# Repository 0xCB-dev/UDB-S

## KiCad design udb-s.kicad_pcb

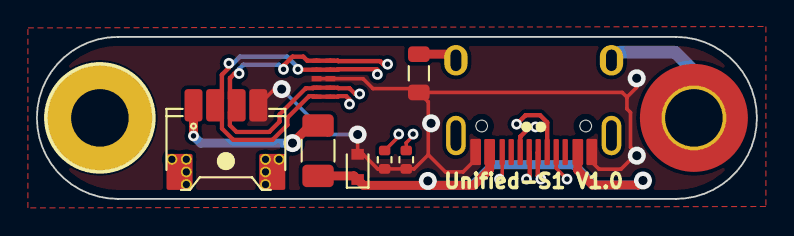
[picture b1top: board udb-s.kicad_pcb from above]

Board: 4 copper layers, 40.0 x 9.0 mm, 10 parts (0 on the bottom side), 8 nets.

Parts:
D1: ESD5Z5V0; D_SOD-523
F1: SMD0805-050-16V; Fuse_1206_3216Metric
FB1: GZ2012D601TF; L_0805_2012Metric
H1: MountingHole; MountingHole_3.2mm_M3_DIN965_Pad_TopBottom
H2: MountingHole; MountingHole_3.2mm_M3_DIN965_Pad_TopOnly
J1: TYPE-C-31-M-12; HRO-TYPE-C-31-M-12-Assembly
J2: 78171-0004; PicoEZMate-Reinforced-Lite
R1, R2: 5.1k; R_0402_1005Metric
U1: TPD4E05U06DQAR; USON-10_2.5x1.0mm_P0.5mm

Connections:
5V: F1.2, J2.1
D+: J1.A6 (D+), J1.B6 (D+), J2.3, U1.1 (IO1), U1.4 (D2+), U1.7 (NC), U1.10 (NC)
D-: J1.A7 (D-), J1.B7 (D-), J2.2, U1.2 (IO2), U1.5 (D2-), U1.6 (NC), U1.9 (NC)
GND: D1.2 (A2), FB1.2, J1.A1 (GND), J1.B1 (GND), J2.4, R1.1, R2.2, U1.3 (GND), U1.8 (GND)
GNDPWR: FB1.1, H1.1, J1.S1 (SHIELD)
unnamed: J1.A5 (CC1), R1.2
unnamed: J1.B5 (CC2), R2.1
VBUS: D1.1 (A1), F1.1, J1.A4 (VBUS), J1.B4 (VBUS)

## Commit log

2023-02-11 added kikit panel assembly
